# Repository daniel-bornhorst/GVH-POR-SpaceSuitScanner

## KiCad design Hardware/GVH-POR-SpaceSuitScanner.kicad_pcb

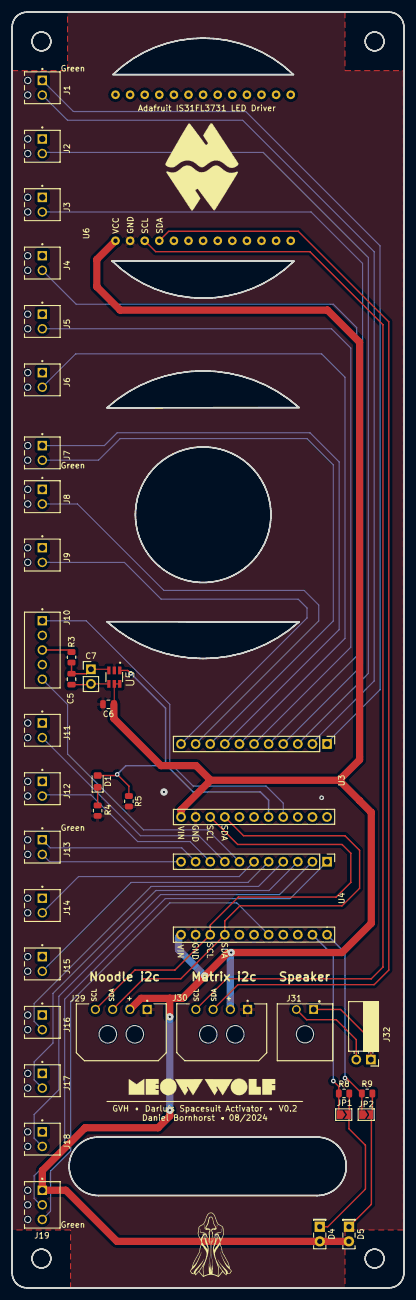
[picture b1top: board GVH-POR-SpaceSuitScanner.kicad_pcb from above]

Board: 2 copper layers, 68.1 x 221.9 mm, 40 parts (0 on the bottom side), 41 nets.

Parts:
C5: 22nF; C_0805_2012Metric
C6: 0.1uF; C_0805_2012Metric
C7: 22nF; PinHeader_1x02_P2.54mm_Vertical
D1: LED_Small; LED_0805_2012Metric_Pad1.15x1.40mm_HandSolder
D4, D5: LED_Small; LED_Rectangular_W5.0mm_H2.0mm
J1, J2, J3, J4, J5, J6, J7, J8, J9, J11, J12, J13, J14, J15, J16, J17, J18: Phoenix _725656; PHOENIX_1725656-2POS
J10: Phoenix_5POS_1725685; PHOENIX_1725685-5POS
J19: Phoenix_3POS_1725669; PHOENIX_1725669-3POS
J29: n00d i2c; MOLEX_MICROFIT-RA-4POS
J30: Matrix i2c; MOLEX_MICROFIT-RA-4POS
J31: Speaker In; MOLEX_MICROFIT-RA-2POS
J32: Speaker; PinSocket_1x02_P2.54mm_Horizontal
JP1, JP2: SolderJumper_2_Open; SolderJumper-2_P1.3mm_Open_TrianglePad1.0x1.5mm
R3, R5: 10K; R_0805_2012Metric
R4: 1K; R_0805_2012Metric
R8, R9: 220; R_0805_2012Metric
U3, U4: AW9523 Expander; Adafruit_AW9523_GPIO_Expander
U5: AT42QT1010; SOT95P270X145-6N
U6: IS31FL3731 LED Driver; Adafruit IS31FL3731 LED Driver

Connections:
CAP_WIRE: J10.3, R3.2
GND: C6.2, J29.1, J30.1, R4.1, R5.2, U3.13 (GND), U4.13 (GND), U5.2 (VSS), U6.2 (GND)
MATRIX_SCL: J30.4, U6.3 (SCL)
MATRIX_SDA: J30.3, U6.4 (SDA)
NOOD_SCL: J29.4, U3.14 (SCL), U4.14 (SCL)
NOOD_SDA: J29.3, U3.15 (SDA), U4.15 (SDA)
unnamed: D1.1 (K), R4.2
unnamed: D4.1 (K), JP1.2 (B), R8.2
unnamed: D5.1 (K), JP2.2 (B), R9.2
unnamed: J31.1, J32.1
unnamed: J31.2, J32.2
unnamed: C5.2, C7.2, U5.4 (SNS)
unnamed: C5.1, C7.1, R3.1, U5.3 (SNSK)
P01_1: J1.1, U3.1
P01_2: J1.2, U3.2
P01_3: J2.2, U3.3
P01_4: J3.2, U3.4
P01_5: J4.2, U3.5
P01_6: J5.2, U3.6
P01_7: J6.2, U3.7
P02_0: JP2.1 (A), R9.1, U4.22 (0)
P02_1: J19.2, U4.1
P02_2: J18.2, U4.2
P02_3: J17.2, U4.3
P02_4: J16.2, U4.4
P02_5: J15.2, U4.5
P02_6: J14.2, U4.6
P02_7: J10.5, U4.7
P11_0: D1.2 (A), R5.1, U3.18 (8), U5.1 (OUT)
P11_1: J10.1, U3.19 (9)
P11_4: J7.1, U3.8 (12)
P11_5: J7.2, U3.9 (13)
P11_6: J8.2, U3.10 (14)
P11_7: J9.2, U3.11 (15)
P12_0: J19.3, U4.18 (8)
P12_3: JP1.1 (A), R8.1, U4.21 (11)
P12_4: J11.2, U4.8 (12)
P12_5: J12.2, U4.9 (13)
P12_6: J13.1, U4.10 (14)
P12_7: J13.2, U4.11 (15)
VCC: C6.1, D4.2 (A), D5.2 (A), J19.1, J29.2, J30.2, U3.12 (VIN), U4.12 (VIN), U5.5 (VDD), U5.6 (SYNC), U6.1 (VCC)

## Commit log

2024-05-06 State Machine scaffolding added
2024-05-06 Achieved Scan up and down
2024-05-06 Added scan release handling
2024-05-06 Further fleshed out the hand scanner sequence
2024-05-06 Added 2x hand scanning. Adjusted timings.
2024-05-22 Added all the states with tweaks to timing
2024-08-01 File housekeeping
2024-08-01 Relocated folder locally and added PCB layout to repo
2024-08-04 A ton of PCB Work
2024-08-11 Schematic progress
2024-08-11 Continuing PCB Layout Process
2024-08-12 Finished laying out PCB
2024-08-12 backing up
2024-08-12 Added pull down resistor to touch output
2024-08-16 Backing up again
2024-08-23 Added silkscreen graphics and signature. Ready for fab.
2024-08-24 PCB Ordered. First version of design archived
2025-01-30 Changed the library symbols to be project specific
